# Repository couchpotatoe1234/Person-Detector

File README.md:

# Person-Detector
A IR laser that detects people coming into your room.

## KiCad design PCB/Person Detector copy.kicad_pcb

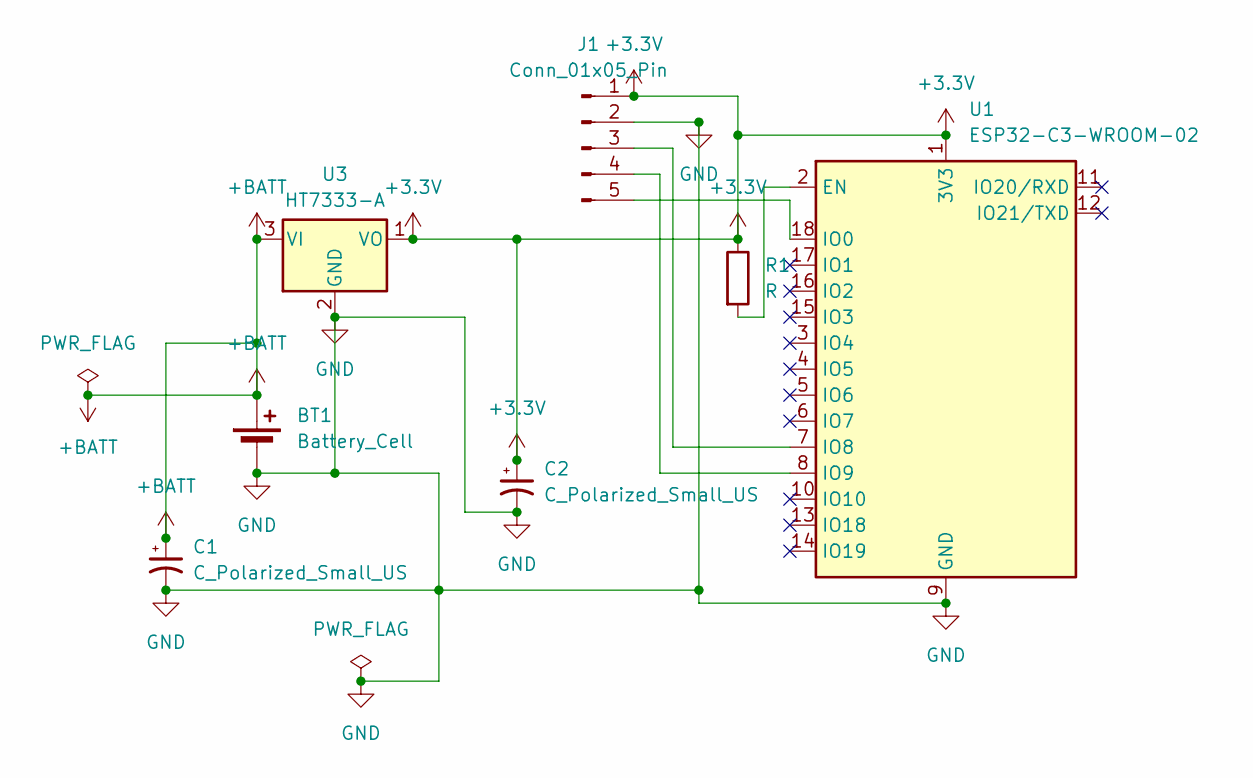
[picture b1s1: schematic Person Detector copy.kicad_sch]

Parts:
BT1: Battery_Cell; BatteryHolder_Keystone_1042_1x18650
C1, C2: C_Polarized_Small_US; CP_Radial_D5.0mm_P2.00mm
J1: Conn_01x05_Pin; PinHeader_1x05_P2.54mm_Vertical
R1: R; R_Axial_DIN0207_L6.3mm_D2.5mm_P7.62mm_Horizontal
U1: ESP32-C3-WROOM-02
U3: HT7333-A; TO-92_Inline

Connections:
+3.3V: C2.1, J1.1, R1.1, U1.1 (3V3), U3.1 (VO)
+BATT: BT1.1 (+), C1.1, U3.3 (VI)
GND: BT1.2 (-), C1.2, C2.2, J1.2, U1.9 (GND), U1.19 (GND), U3.2 (GND)
unnamed: J1.3, U1.7 (IO8)
unnamed: J1.4, U1.8 (IO9)
unnamed: J1.5, U1.18 (IO0)
unnamed: R1.2, U1.2 (EN)

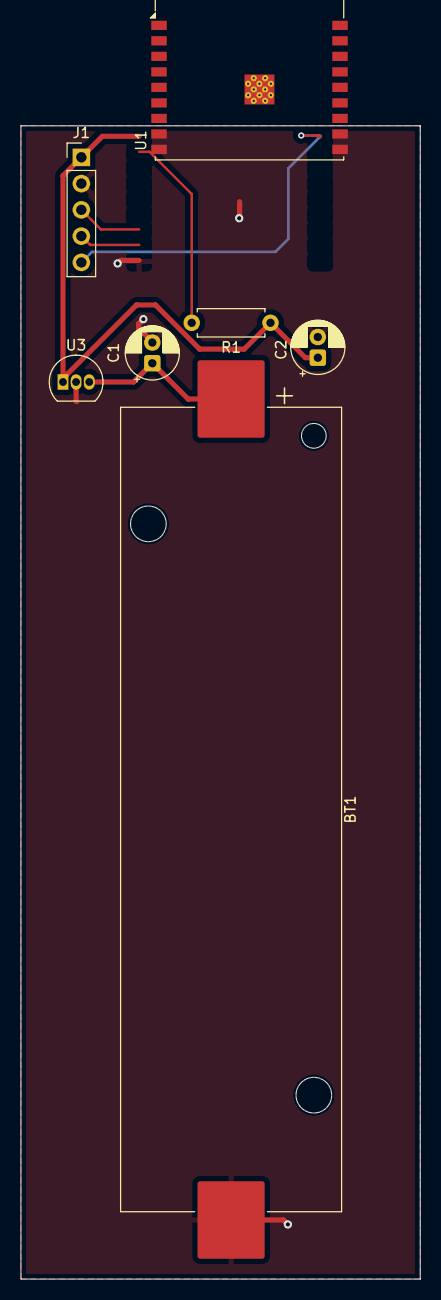
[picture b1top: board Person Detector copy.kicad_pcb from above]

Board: 2 copper layers, 38.6 x 111.5 mm, 7 parts (0 on the bottom side), 7 nets.

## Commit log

2026-03-16 commit 1
2026-03-17 commit 2
2026-03-17 commit 3
2026-03-18 CAD stuff
